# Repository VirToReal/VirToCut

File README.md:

ATTENTION
==============================
I moved my repositories to gitlab, please do any suggestions there: https://gitlab.com/Hirmer/VirToCut

Thank you!

# VirToCut

## What is this?
This is a Plate Saw Machine, which cuts straight stripes from a plate. The machine can be controlled via Software automatically, or trough the software/control-panel manually. The cutting-distance of the saw blade and the material feed, too. The thickness of the saw blade will be added automatically in manual-mode.

To control the saw via software in automatic-mode, you can use a code syntax i developed for this machine which will look like that:
```
A50 B300 // Feed Material 50mm and cut into that material 300mm.
A50 B300
A30 B300
A30 B300
A10 B300
ROTATE // Saw stops, user have to rotate the plate 90°, some visual assistance shows user which stripes have to be placed into the machine (not ready yet) and confirms via software/hardware- button.
A100 B100
A100 B100
WAIT // Saw stops, user have to place a new pair of stripes into the machine and confirms to proceed.
A80 B60
A80 B60
WAIT // Saw stops, user have to place a new pair of stripes into the machine and confirms to proceed.
A50 B20
A50 B20
A50 B20
```
The result will look like this:

## About the project
This is a project about building and controlling a Plate Saw Machine. You can generate your own components by using the "ConstructionTemplate.scad"-File with OpenSCAD (http://www.openscad.org). Every component are adjustable in their dimensions as described in the “OpenScadDokumentation”-Folder. In OpenSCAD you also able to switch between the complete overview as the picture below and each single printable part as listened in the “OpenScadDokumentation”-Folder by using the “printmode”-Variable within the “ConstructionTemplate.scad”-File. All details are described in the file itself. 

## Necessary experience and software
To get this project to work, you need some experience in printing parts with a 3D-Printer. Also some knowledge in electrical engineering are required, because you have to make a PCB and wire up a power-supply, raspberry-pi and an arduino-mega-2560 + ramps-shield. My files for milling/etching the PCB are to be found in the "KiCad"-Folder. The Files can be edited with the KiCad-Software (http://kicad.org). I used FlatCam (http://flatcam.org) to mill the "Gerber"-Files from KiCad.

## Software used in this project
I use Python to send G-Code-Commands from the Raspberry-Pi to the Arduino over a serial interface. Marlin (http://marlinfw.org) is running on the Arduino and interprets the received G-Code-Commands and drives the engines with the RAMPS1.4 Shield (http://reprap.org/wiki/RAMPS_1.4). My Marlin-Configuration can be found in the "Marlin Firmware"-Folder. 

The Python-Software can be found in the "Python Software"-Folder. At the moment its only available in German. If its necessary, I will rewrite it in english, too. The Software is already able to generate saw-pattern-templates, to cut a plate in different sized plates automatically. 

- Homescreen

- Configuration-Windows

But consider, the project is not fully completed yet. Some smaller improvements still has to be made:
- Structure on the material feeder, which prevents the material from rotating. Thought on something like a feather tensioned clamp. 
- Some smaller software updates (don't find the time at the moment). 

  Any help would be appreciated.

Contact me if you want futher informations!

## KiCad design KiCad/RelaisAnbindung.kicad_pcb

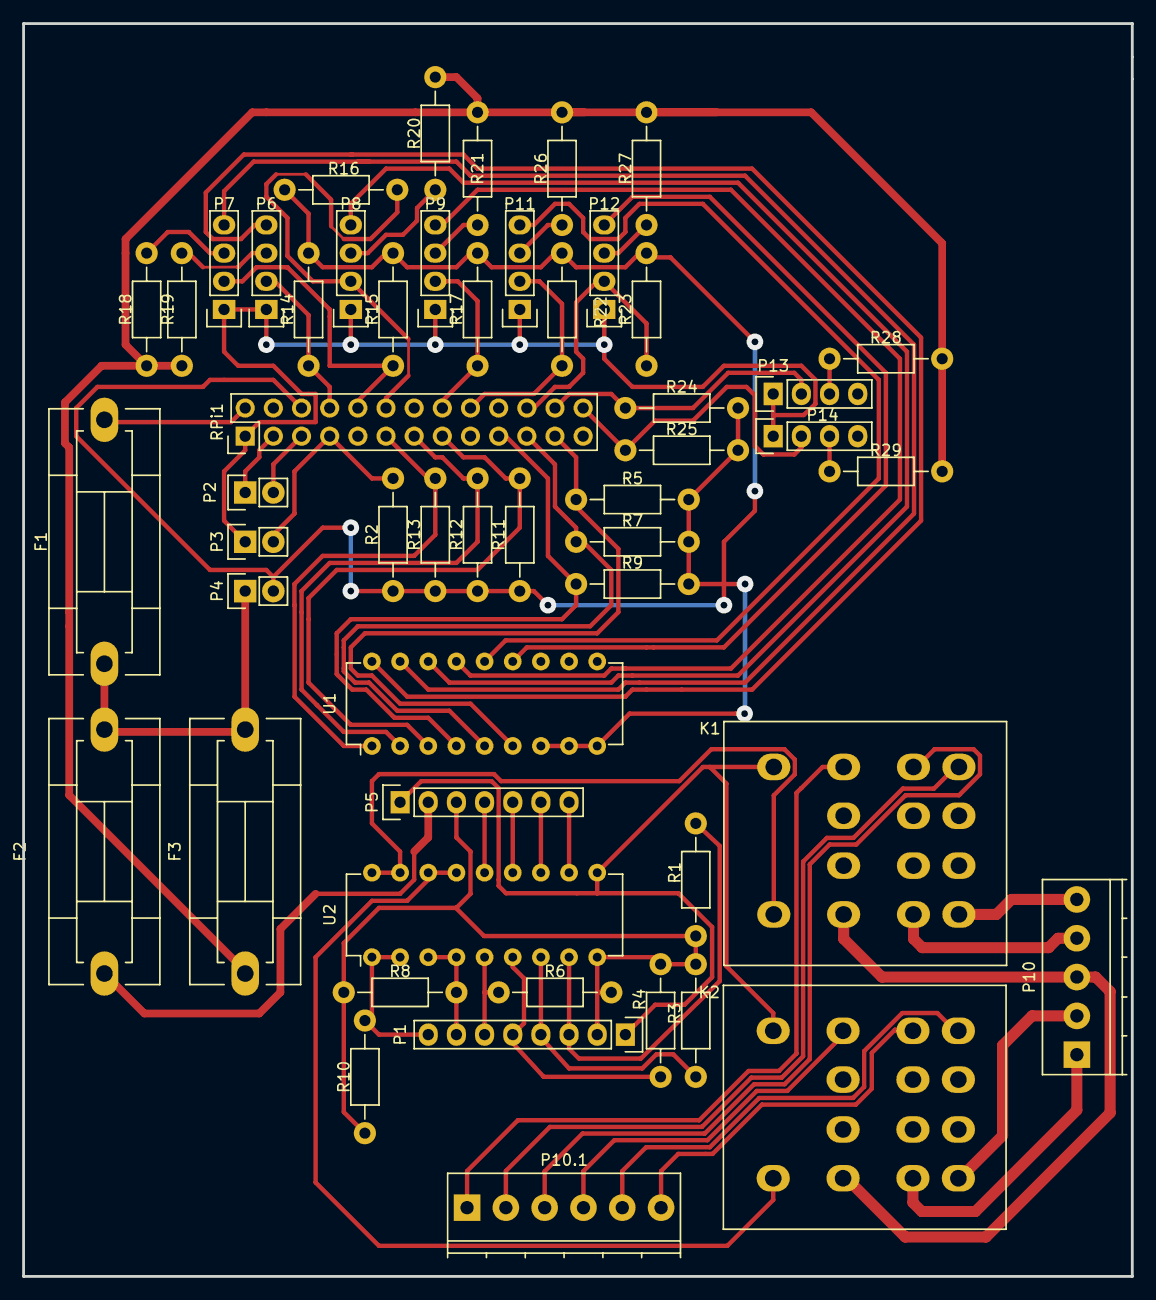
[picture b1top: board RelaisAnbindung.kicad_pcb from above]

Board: 2 copper layers, 100.0 x 113.0 mm, 52 parts (0 on the bottom side), 62 nets.

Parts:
F1, F2, F3: 1A; Fuseholder5x20_horiz_SemiClosed_Casing10x25mm
K1: RELAY_Stbsgr; Relais_FIN94_Print-Socket
K2: RELAY_Hakrsae; Relais_FIN94_Print-Socket
P1: CONN_SUPPLY2; Pin_Header_Straight_1x08
P2: CONN_I^2C; Pin_Header_Straight_1x02
P3: CONN_Not-Aus; Pin_Header_Straight_1x02
P4: CONN_SUPPLY; Pin_Header_Straight_1x02
P5: CONN_Aux_Res; Pin_Header_Straight_1x07
P6: CONN_TV_Vr; Pin_Header_Straight_1x04
P7: CONN_TV_Zk; Pin_Header_Straight_1x04
P8: CONN_TV_GZk; Pin_Header_Straight_1x04
P9: CONN_TS_Vr; Pin_Header_Straight_1x04
P10: CONN_01X05; TerminalBlock_Pheonix_PT-3.5mm_5pol
P10.1: CONN_01X06; TerminalBlock_Pheonix_PT-3.5mm_6pol
P11: CONN_TS_Zk; Pin_Header_Straight_1x04
P12: CONN_TS_Snt; Pin_Header_Straight_1x04
P13, P14: CONN_T_Res; Pin_Header_Straight_1x04
R1, R2, R3, R4, R5, R6, R7, R8, R9, R10, R11, R12, R13, R14, R15, R16, R17, R22, R23, R24, R25: R10k; Resistor_Horizontal_RM10mm
R18, R19, R20, R21, R26, R27, R28, R29: R340; Resistor_Horizontal_RM10mm
RPi1: RASPBERRY_IO; Pin_Header_Straight_2x13
U1, U2: ULN2803; DIP-18_W7.62mm

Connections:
unnamed: F1.1, F2.2, F3.2, P4.1
unnamed: F1.2, RPi1.2
unnamed: F2.1, P5.2
unnamed: F3.1, R18.2, R19.2, R20.2, R21.2, R26.2, R27.2, R28.2, R29.2
unnamed: K1.1, P10.5
unnamed: K1.4, P10.1.2
unnamed: K1.5, P10.4
unnamed: K1.8, P10.1.3
unnamed: K1.9, K2.9, P10.3
unnamed: K1.12, P10.1.1
unnamed: K1.13, U2.17, U2.18
unnamed: K1.14, K2.14, P1.1, P5.1, U2.10
unnamed: K2.1, P10.2
unnamed: K2.4, P10.1.5
unnamed: K2.5, P10.1
unnamed: K2.8, P10.1.6
unnamed: K2.12, P10.1.4
unnamed: K2.13, U2.15, U2.16
unnamed: P1.2, P5.3, R1.2, R3.2, R4.2, R6.2, R8.2, R10.2, U2.9
unnamed: P1.3, R1.1, U2.8
unnamed: P1.4, R3.1, U2.7
unnamed: P1.5, R4.1, U2.6
unnamed: P1.6, R6.1, U2.5
unnamed: P1.7, R8.1, U2.3, U2.4
unnamed: P1.8, R10.1, U2.1, U2.2
unnamed: P2.1, RPi1.3
unnamed: P2.2, RPi1.5
unnamed: P3.2, R2.2, RPi1.7
unnamed: P4.2, R2.1, R5.1, R7.1, R9.1, R11.1, R12.1, R13.1, R14.1, R15.1, R16.1, R17.1, R22.1, R23.1, R24.1, R25.1, RPi1.6, U1.7, U1.8, U1.9
unnamed: P5.4, U2.14
unnamed: P5.5, U2.13
unnamed: P5.6, U2.12
unnamed: P5.7, U2.11
unnamed: P6.2, R14.2, RPi1.8
unnamed: P6.3, R18.1
unnamed: P6.4, U1.18
unnamed: P7.2, R15.2, RPi1.10
unnamed: P7.3, R19.1
unnamed: P7.4, U1.17
unnamed: P8.2, R16.2, RPi1.12
unnamed: P8.3, R20.1
unnamed: P8.4, U1.16
unnamed: P9.2, R17.2, RPi1.16
unnamed: P9.3, R21.1
unnamed: P9.4, U1.15
unnamed: P3.1, P6.1, P7.1, P8.1, P9.1, P11.1, P12.1, P13.1, P14.1, RPi1.1
unnamed: P11.2, R22.2, RPi1.18
unnamed: P11.3, R26.1
unnamed: P11.4, U1.14
unnamed: P12.2, R23.2, RPi1.22
unnamed: P12.3, R27.1
unnamed: P12.4, U1.13
unnamed: P13.2, R24.2, RPi1.24
unnamed: P13.3, R28.1
unnamed: P14.2, R25.2, RPi1.26
unnamed: P14.3, R29.1
unnamed: R5.2, RPi1.23, U1.6
unnamed: R7.2, RPi1.21, U1.5
unnamed: R9.2, RPi1.19, U1.4
unnamed: R11.2, RPi1.15, U1.3
unnamed: R12.2, RPi1.13, U1.2
unnamed: R13.2, RPi1.11, U1.1

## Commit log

2016-11-20 Add files via upload
    early release of the Plate-Saw-Machine, still work to do
2016-11-20 Update ConstructingTemplate.scad
    whoops
2016-11-25 Add files via upload
    First Version of the software which is capable of cutting something ;-)
2016-11-27 Update CommandsStack.py
    added <max_cut> value to use in G-Code Workstations
2016-12-02 Add files via upload
    Tools / searching for G28 Command for calibrating absolute Y-Axis position (not tested yet)
    Dialogs / added 'distance of blade to left stop' to settings/parameters
    CommandsStack / fixed positioning information of feeder, added more safety functions etc.
    ControllGUI_9.glade / added absolute Y-Axis position and an expander under Settings/G-Codes with placeholder informations
    ControllGUI / several changes caused from the alterings above
    GPIO / new effect, not tested yet
2016-12-09 Add files via upload
    Several bug-fixes, improved manual movement and tested behavior on running machine
2016-12-11 Add files via upload
    Fixed wrong interpretation of movement coordinates
2016-12-11 Add files via upload
    woops...
2016-12-11 Add files via upload
    corrected "vorschub" interpretation, but still not final
2016-12-17 Correct interpreting of cutting direction
    implemented correct cutting direction interpreting by searching through the "Schneiden" working-step for the <max_cut> placeholder.
2016-12-21 safety cut distance
    added safety cut distance to max_cut variable to prevent blade collision at feeding
2016-12-21 fixed Booting blinking
2016-12-25 Add files via upload
    adjusting software remote via webcam, forgot to remount the webcam, but nice shot anyway
2016-12-25 Add files via upload
    Proper GPIO cleanup after exiting
2016-12-25 Added saw movement controll
    controlling if there is enough space for the saw to move via hardware-buttons
2016-12-27 added Forcing max. Cuttingdistance
    this Togglebutton in the Status-Tab in the sidemenu will allow the user to force the temporary position of the saw declared to be the max. position. So the user don't need to completely extend the sa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
2017-01-07 Added Button-Press-Time operation
    Added minimal Presstime for each hardware-button
    Added long presstime for advanced operations
    (not tested yet)
2017-03-03 Fixed bad Hardware-Button behavior, PowerSupply management
    Added Queue for HardwareButtons because GTK dont like called functions in threads, which would be called via interrupt on the GPIO edge detection.
    Added automatic PowerSupply Power ON / OFF
    - not tested yet ;-) -
2017-03-05 Fixed behavieur of PS and Saw-Hardwarebutton
    - now the PowerSupply correctly turns on/off
    - Saw-Hardwarebutton now works and supplys the Pusher-Override-Mode
2017-03-22 Add files via upload
    Added Picture-Description of each printable Part
2017-03-22 fixed bad saw-direction support
    Software should now consider the direction of the saw-blade at its programmed G-Code
2020-07-19 Update README.md
    moved repository to gitlab
2021-11-10 Update README.md
    https://forum.kicad.info/t/warning-avoid-all-links-to-kicad-pcb-org-use-kicad-org/31521
